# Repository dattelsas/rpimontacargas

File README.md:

# rpimontacargas
Repositorio del Sistemas de Cámaras para Montacargas

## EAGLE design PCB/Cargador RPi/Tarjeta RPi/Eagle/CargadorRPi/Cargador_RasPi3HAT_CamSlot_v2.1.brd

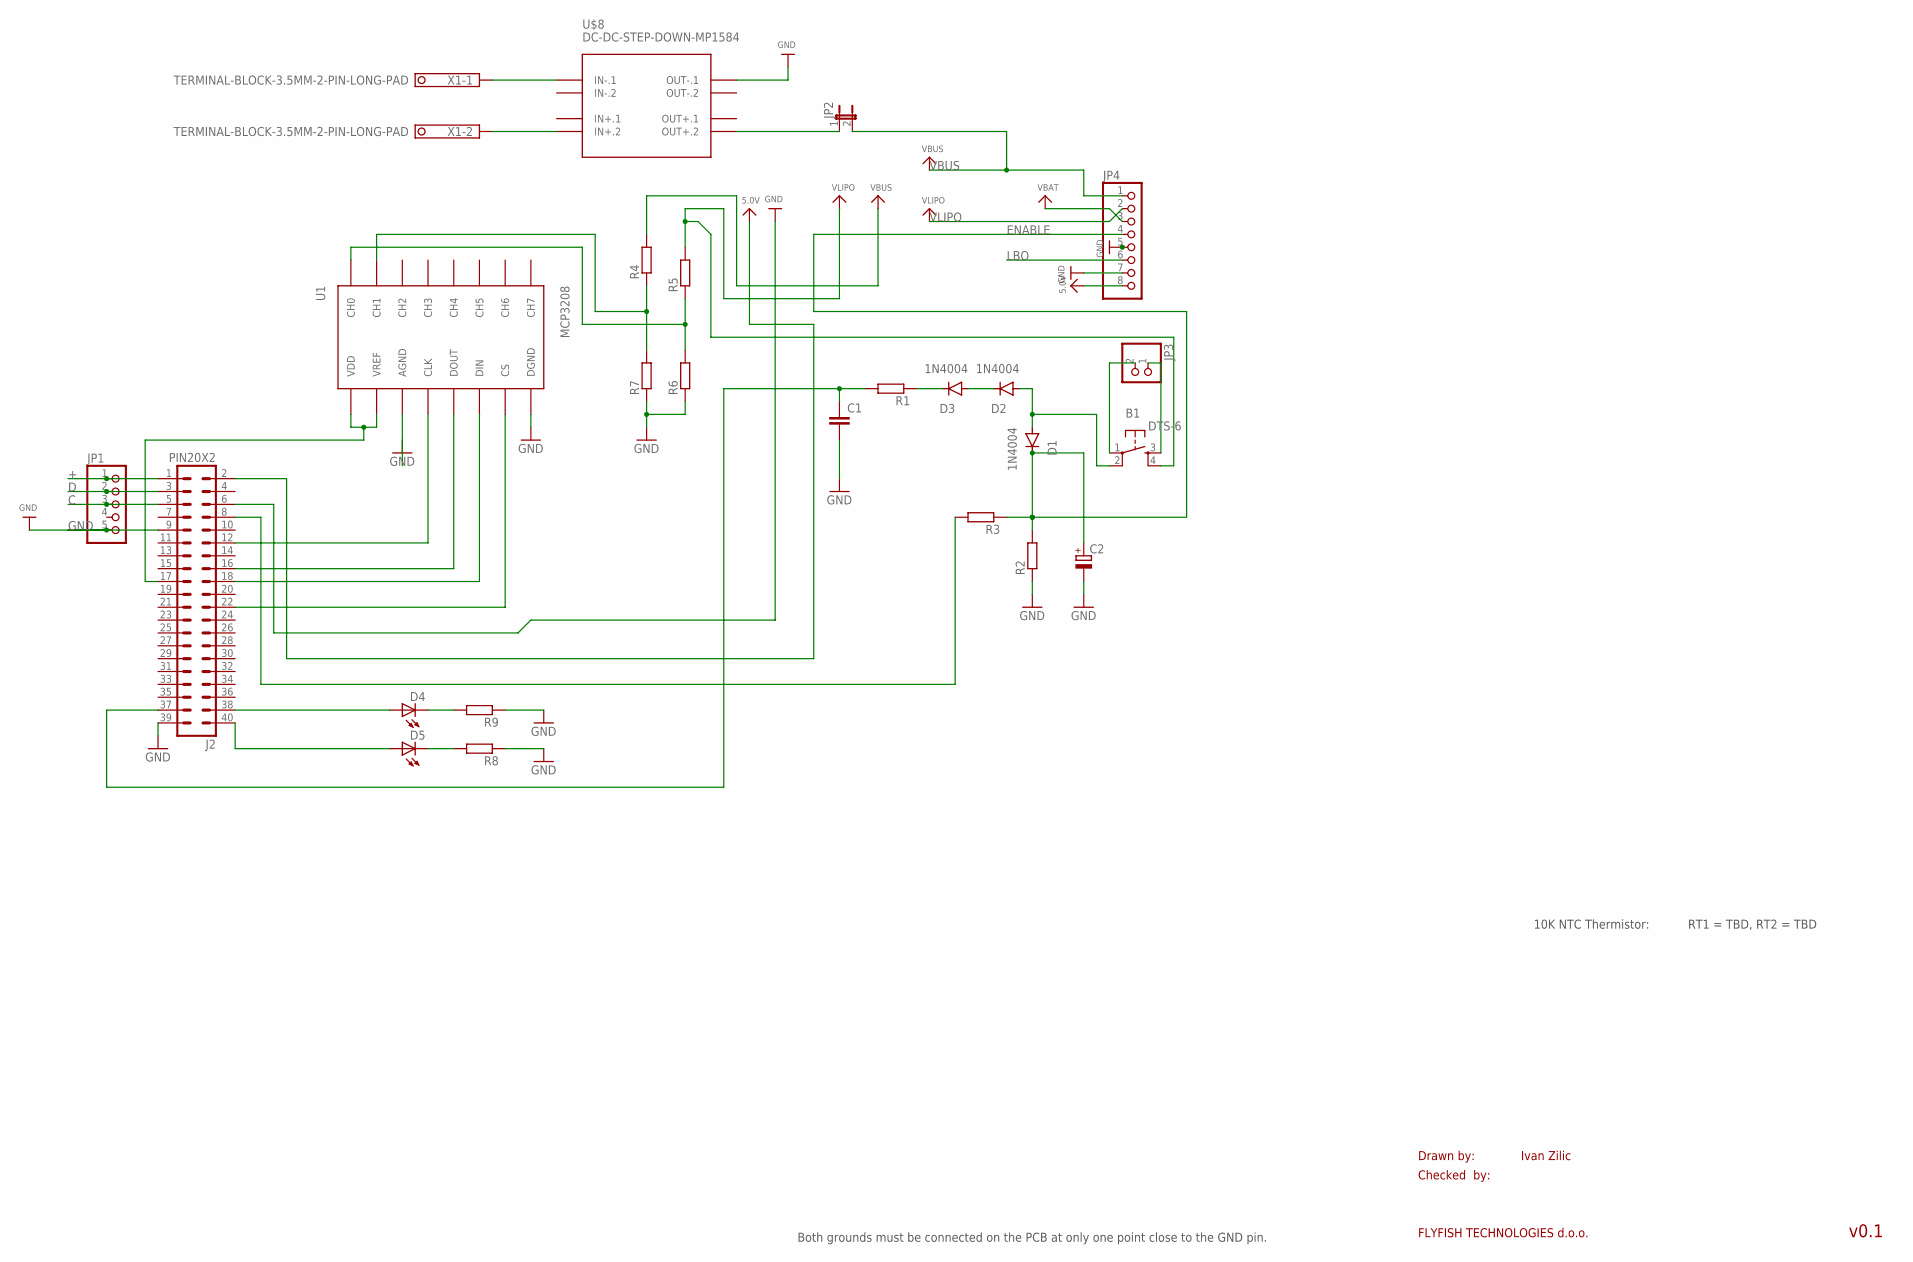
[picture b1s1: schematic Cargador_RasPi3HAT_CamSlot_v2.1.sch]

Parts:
B1: DTS-6
C1: C2.5/2; C2.5-2
C2: CPOL-EUE5-4; E5-4
D1, D2, D3: 1N4004; DO41-10
D4, D5: LED_ELD260; LED_LD260
J2: PIN20X2; PIN_20X2
JP1: PINHD-1X5; 1X05
JP2: JP1E; JP1
JP3: PINHD-1X2; 1X02
JP4: HEADER-1X8; 1X08_OVAL
R1, R2, R3, R4, R5, R6, R7, R8, R9: R-EU_0207/10; 0207/10
U1: MCP3208; DIL16
U$8: DC-DC-STEP-DOWN-MP1584
X1: TERMINAL-BLOCK-3.5MM-2-PIN-LONG-PAD; TERMINAL-BLOCK-2-PIN-3.5MM-LONG-PAD

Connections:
5.0V: J2.2, JP4.8
+: J2.1, JP1.1
C: J2.5, JP1.3
D: J2.3, JP1.2
ENABLE: C2.+, D1.C, JP4.4, R2.2, R3.1
GND: C1.2, C2.-, J2.6, J2.9, J2.39, JP1.5, JP4.5, JP4.7, R2.1, R6.1, R7.1, R8.1, R9.1, U1.AGND, U1.DGND, U$8.OUT-.1
LBO: JP4.6
unnamed: B1.1, JP3.2
unnamed: B1.3, JP3.1
unnamed: D4.K (C), R9.2
unnamed: D5.K (C), R8.2
unnamed: D3.C, R1.1
unnamed: D5.A, J2.40
unnamed: D4.A, J2.38
unnamed: U$8.IN-.1, X1.1
unnamed: U$8.IN+.2, X1.2
unnamed: JP2.1, U$8.OUT+.2
unnamed: J2.17, U1.VDD, U1.VREF
unnamed: R4.1, R7.2, U1.CH1
unnamed: R5.1, R6.2, U1.CH0
unnamed: J2.8, R3.2
unnamed: J2.12, U1.CLK
unnamed: J2.22, U1.CS
unnamed: D2.C, D3.A
unnamed: B1.2, D1.A, D2.A
unnamed: J2.18, U1.DIN
unnamed: J2.16, U1.DOUT
unnamed: C1.1, J2.37, R1.2
VBAT: JP4.3
VBUS: JP2.2, JP4.1, R4.2
VLIPO: B1.4, JP4.2, R5.2

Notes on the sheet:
Drawn by:
Checked by:
FLYFISH TECHNOLOGIES d.o.o.
Ivan Zilic
v0.1
Both grounds must be connected on the PCB at only one point close to the GND pin.
10K NTC Thermistor:
RT1 = TBD, RT2 = TBD

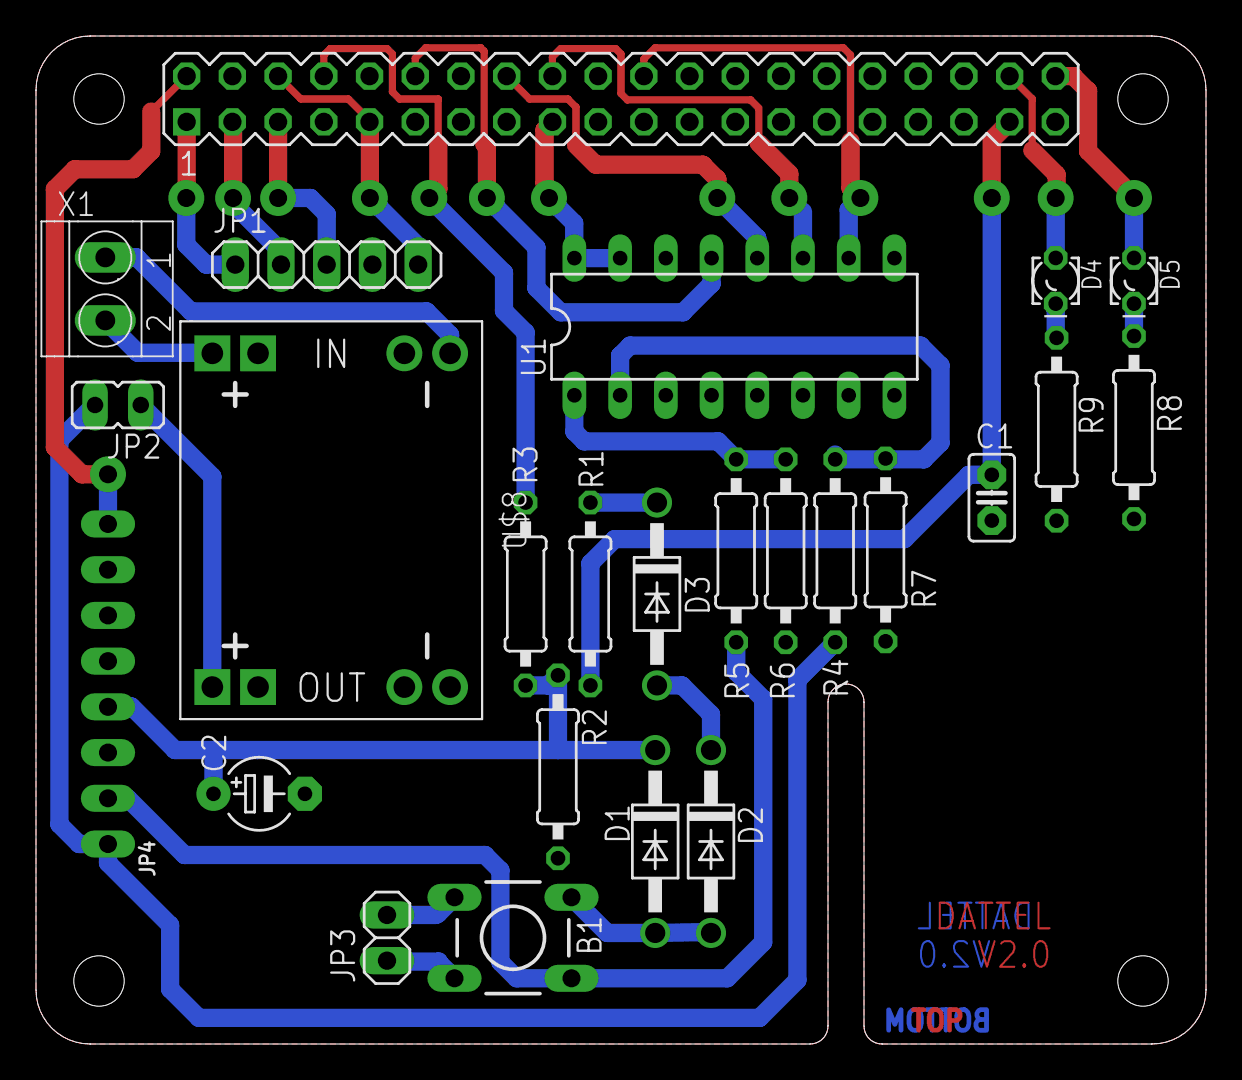
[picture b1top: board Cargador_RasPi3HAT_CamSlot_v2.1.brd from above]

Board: 2 copper layers, 65.0 x 56.0 mm, 25 parts (0 on the bottom side), 29 nets.

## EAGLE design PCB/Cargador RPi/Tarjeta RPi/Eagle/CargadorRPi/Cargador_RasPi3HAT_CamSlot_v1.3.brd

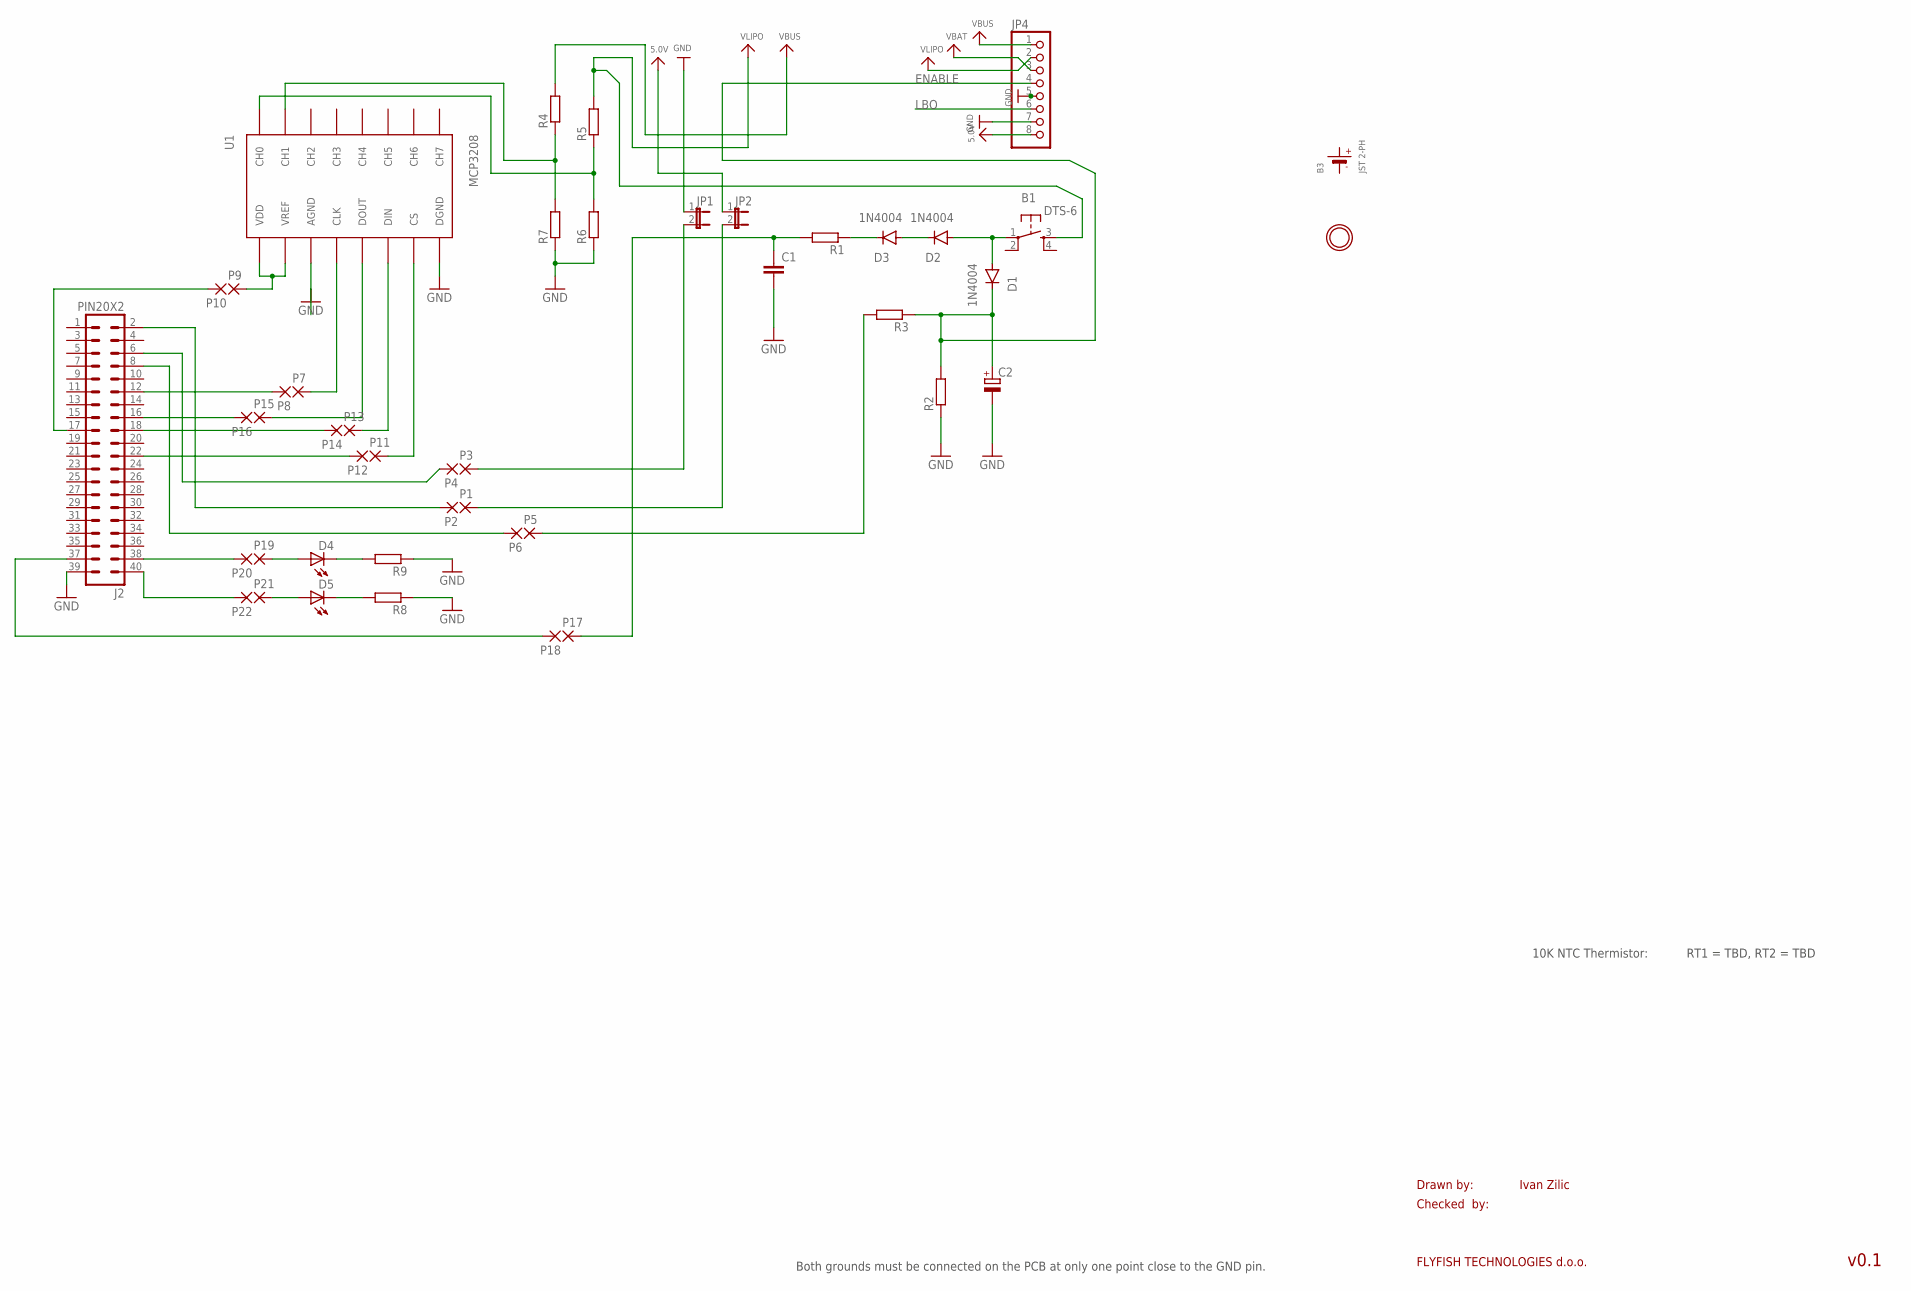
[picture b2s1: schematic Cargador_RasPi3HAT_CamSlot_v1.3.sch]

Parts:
B1: DTS-6
B3: JST 2-PH; JSTPH2
C1: C2.5/2; C2.5-2
C2: CPOL-EUE5-4; E5-4
D1, D2, D3: 1N4004; DO41-10
D4, D5: LED_ELD260; LED_LD260
J2: PIN20X2; PIN_20X2
JP1, JP2: JP1E; JP1
JP4: HEADER-1X8; 1X08_OVAL
P1, P2, P3, P4, P5, P6, P7, P8, P9, P10, P11, P12, P13, P14, P15, P16, P17, P18, P19, P20, P21, P22: 2,15/1,0
R1, R2, R3, R4, R5, R6, R7, R8, R9: R-EU_0207/10; 0207/10
U1: MCP3208; DIL16
U$5: MOUNTINGHOLE2.5; MOUNTINGHOLE_2.5_PLATED

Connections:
5.0V: JP2.1, JP4.8
ENABLE: C2.+, D1.C, JP4.4, R2.2, R3.1
GND: C1.2, C2.-, J2.39, JP1.1, JP4.5, JP4.7, R2.1, R6.1, R7.1, R8.1, R9.1, U1.AGND, U1.DGND
LBO: JP4.6
unnamed: JP1.2, P3.1
unnamed: P5.1, R3.2
unnamed: D4.K (C), R9.2
unnamed: D5.K (C), R8.2
unnamed: D3.C, R1.1
unnamed: J2.40, P22.1
unnamed: J2.38, P20.1
unnamed: P11.1, U1.CS
unnamed: P15.1, U1.DOUT
unnamed: P13.1, U1.DIN
unnamed: P7.1, U1.CLK
unnamed: J2.17, P10.1
unnamed: R4.1, R7.2, U1.CH1
unnamed: R5.1, R6.2, U1.CH0
unnamed: J2.2, P2.1
unnamed: J2.6, P4.1
unnamed: J2.8, P6.1
unnamed: J2.12, P8.1
unnamed: P9.1, U1.VDD, U1.VREF
unnamed: JP2.2, P1.1
unnamed: C1.1, P17.1, R1.2
unnamed: J2.22, P12.1
unnamed: D2.C, D3.A
unnamed: B1.1, D1.A, D2.A
unnamed: J2.18, P14.1
unnamed: J2.16, P16.1
unnamed: J2.37, P18.1
unnamed: D4.A, P19.1
unnamed: D5.A, P21.1
VBAT: JP4.3
VBUS: JP4.1, R4.2
VLIPO: B1.3, JP4.2, R5.2

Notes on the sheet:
Drawn by:
Checked by:
FLYFISH TECHNOLOGIES d.o.o.
Ivan Zilic
v0.1
Both grounds must be connected on the PCB at only one point close to the GND pin.
10K NTC Thermistor:
RT1 = TBD, RT2 = TBD

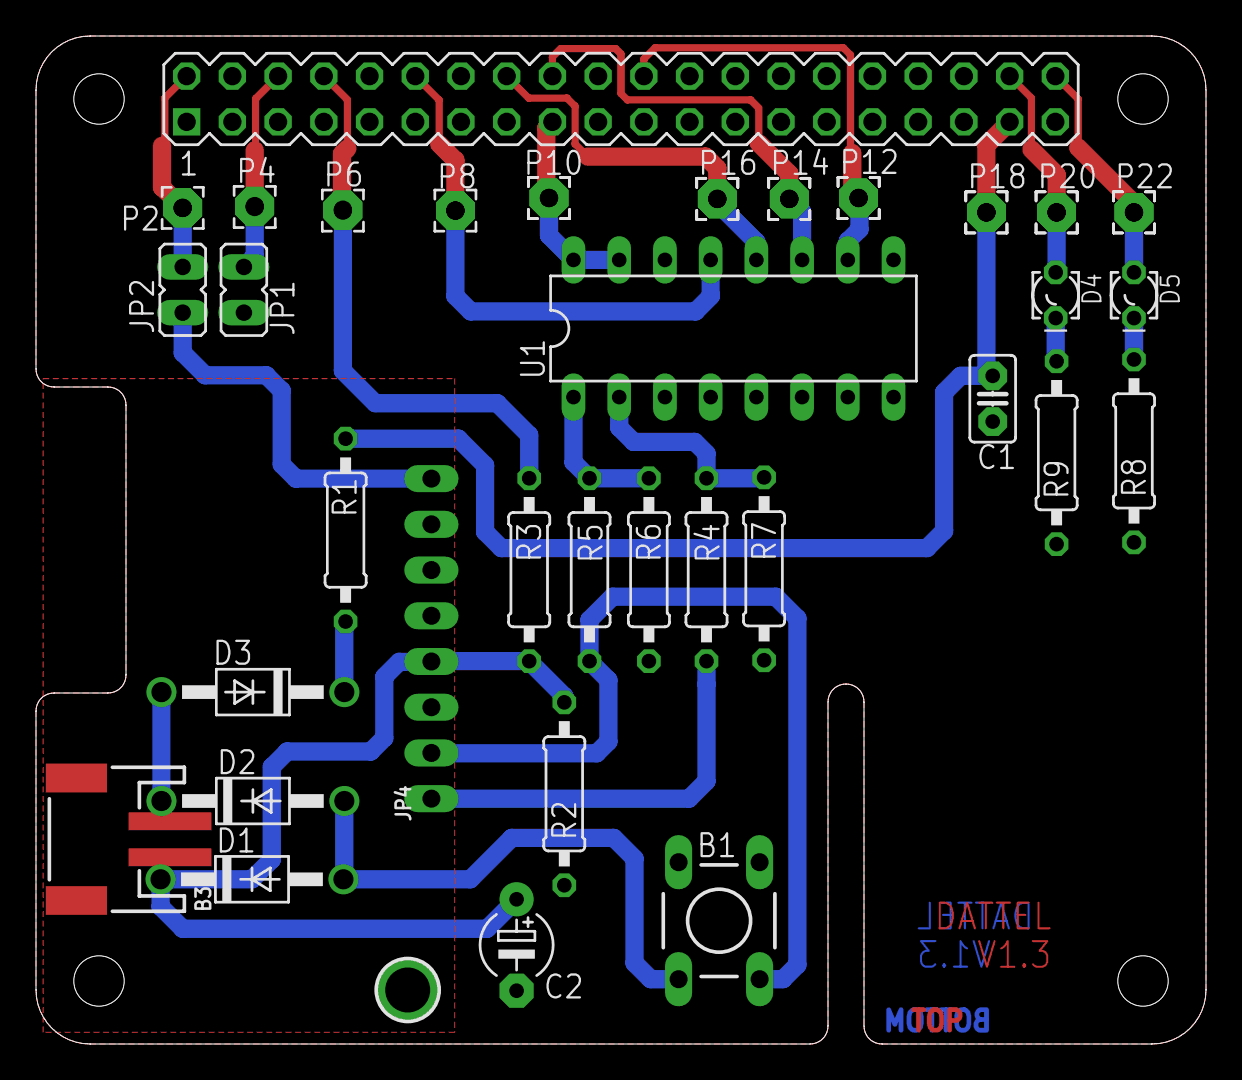
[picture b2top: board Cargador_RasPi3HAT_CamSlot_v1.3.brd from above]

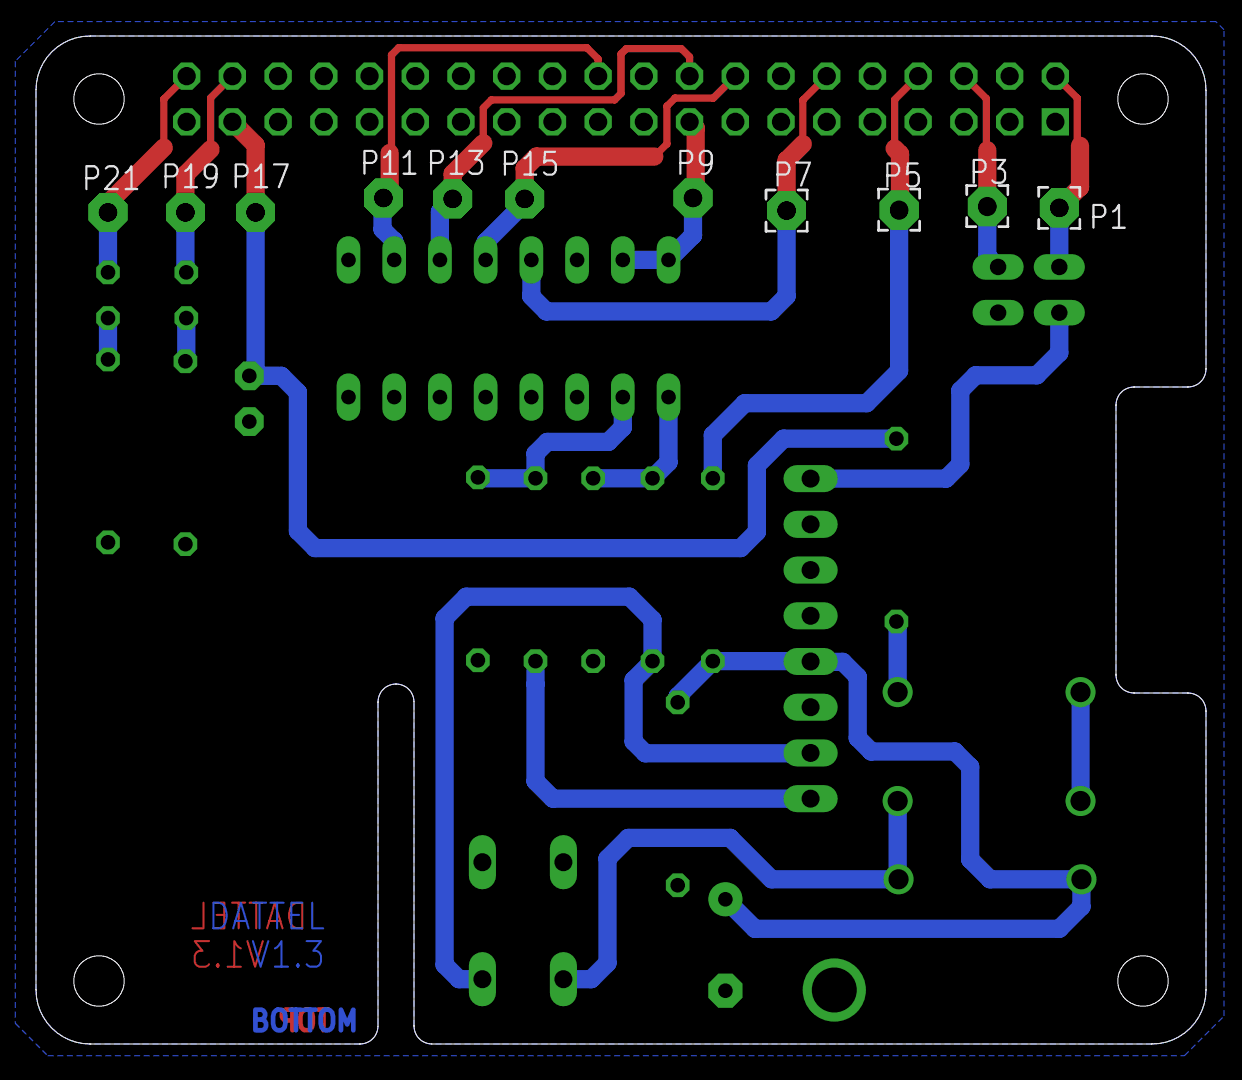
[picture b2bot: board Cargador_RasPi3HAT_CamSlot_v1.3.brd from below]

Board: 2 copper layers, 65.0 x 56.0 mm, 46 parts (4 on the bottom side), 34 nets.

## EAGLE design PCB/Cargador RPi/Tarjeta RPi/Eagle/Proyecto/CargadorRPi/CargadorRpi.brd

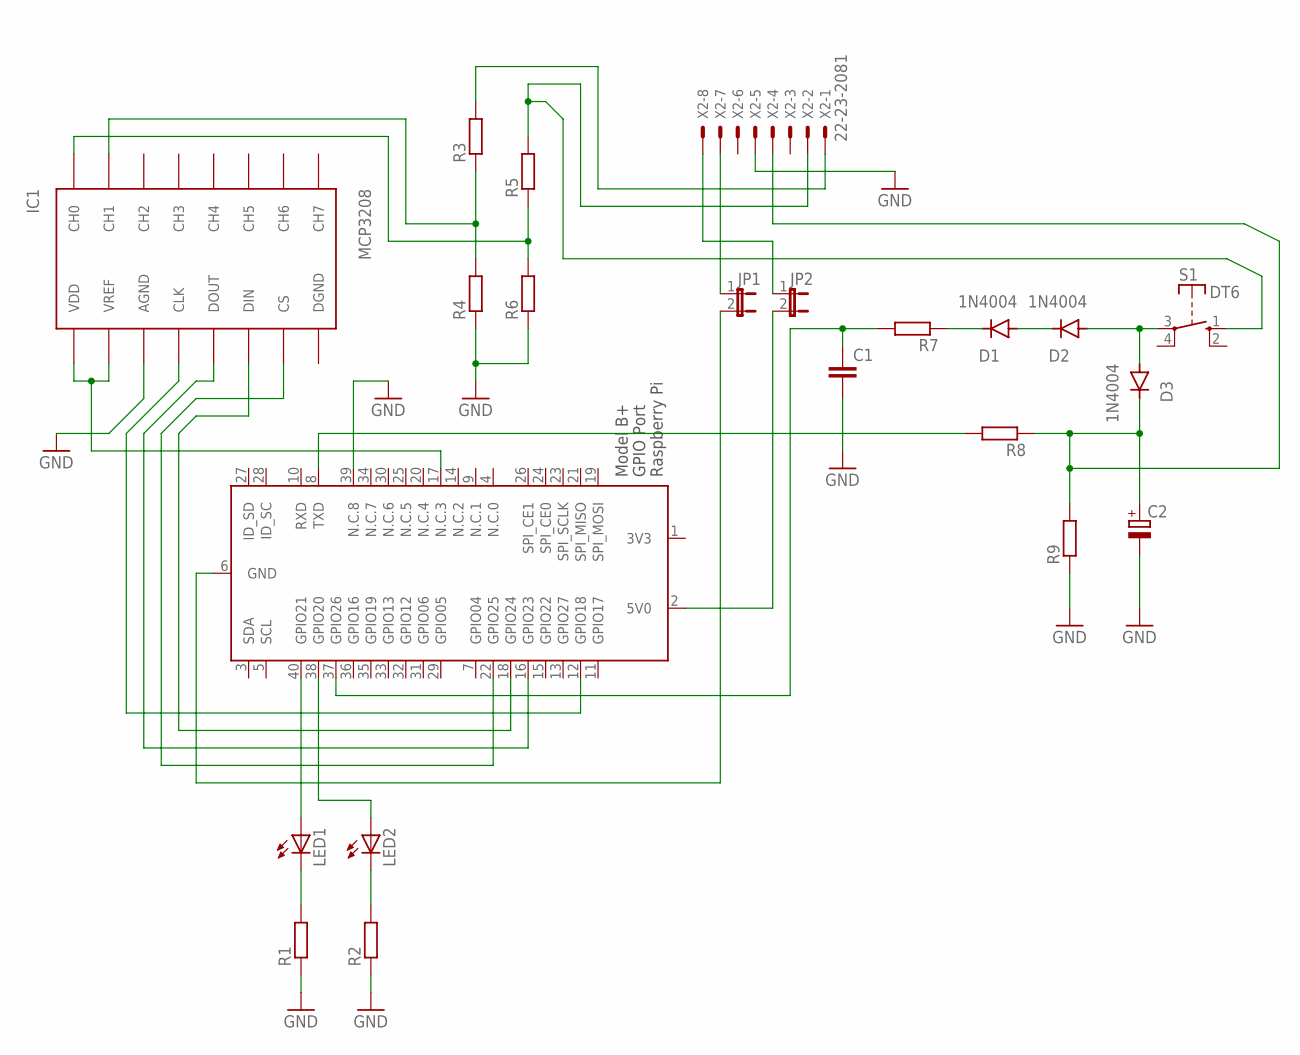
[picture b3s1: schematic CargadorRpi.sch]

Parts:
C1: C2.5/2; C2.5-2
C2: CPOL-EUE5-4; E5-4
D1, D2, D3: 1N4004; DO41-10
IC1: MCP3208; DIL16
JP1, JP2: JP1E; JP1
LED1, LED2: LED_ELD260; LED_LD260
R1, R2, R3, R4, R5, R6, R7, R8, R9: R; R0805
S1: DT6
X1: RASPI_GPIO_B+_PIN
X2: 22-23-2081

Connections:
3V3: X1.1 (3V3)
DGND: IC1.DGND
GND: C1.2, C2.-, IC1.AGND, R1.1, R2.1, R4.1, R6.1, R9.1, X1.39 (N.C.8), X2.5
unnamed: LED1.K (C), R1.2
unnamed: LED2.K (C), R2.2
unnamed: LED1.A, X1.40 (GPIO21)
unnamed: LED2.A, X1.38 (GPIO20)
unnamed: IC1.CS, X1.22 (GPIO25)
unnamed: IC1.DOUT, X1.16 (GPIO23)
unnamed: IC1.DIN, X1.18 (GPIO24)
unnamed: IC1.CLK, X1.12 (GPIO18)
unnamed: IC1.VDD, IC1.VREF, X1.17 (N.C.3)
unnamed: IC1.CH1, R3.1, R4.2
unnamed: IC1.CH0, R5.1, R6.2
unnamed: R3.2, X2.1
unnamed: R5.2, S1.1 (S), X2.2
unnamed: JP1.1, X2.7
unnamed: JP1.2, X1.6 (GND)
unnamed: JP2.1, X2.8
unnamed: JP2.2, X1.2 (5V0)
unnamed: C1.1, R7.2, X1.37 (GPIO26)
unnamed: D1.C, R7.1
unnamed: D1.A, D2.C
unnamed: D2.A, D3.A, S1.3
unnamed: C2.+, D3.C, R8.1, R9.2, X2.4
unnamed: R8.2, X1.8 (TXD)

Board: 2 copper layers, 22 parts (1 on the bottom side), 24 nets, no tracks yet.

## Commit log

2019-01-28 Se agrega archivo .gitignore y se ignora el contenido del directorio Imágenes OS
2019-01-28 Se ignora el contenido del directorio ImgOS
2019-01-28 Se incluyen archivos de diseno del cargador RPi.
2019-01-28 Se actualiza archivo .gitignore
2019-01-28 Diagrama esquemático en Eagle del Cargador RPi.
2019-01-29 Se actualiza el diagrama esquemático del cargador RPi.
2019-01-29 Versión inicial PCB cargador RPi.
2019-01-29 Plantillas PCB HAT
2019-01-29 Se eliminan archivos temporales de proteus
2019-01-29 Se adiciona el archivo explicaci[on scripts oscar paruma
2019-01-30 Se ajusta el diagrama esquemático para utilizar la plantilla RasPi-BplusHAT_CamSlot.sch
2019-01-31 Se borran archivos temporales generados por Eagle.
2019-01-31 Se reemplaza pulsador en el diagrama esquemático.
2019-01-31 Se agrega librería de switches para Eagle.
2019-01-31 Se modifica la PCB aumentando el ancho de los trazos.
2019-01-31 Versión para redistribuir los componentes.
2019-01-31 Se ignoran archivos temporales generados por Eagle y Proteus.
2019-02-02 Ajustes para fabricación de PCB.
2019-02-02 Ajustes teniendo en cuenta la orientación del conector GPIO.
2019-02-02 Se ignora archivo temporal generado por Eagle.
2019-02-07 Se borran versiones no utilizadas y se organiza la estructura de directorios.
2019-02-07 Librería que contiene los holes para los postes del booster.
2019-02-07 Se organiza la estructura de directorios y se genera una nueva versión de la PCB que no requiere through-hole.
2019-02-09 Scripts originales para monitoreo y control del cargador RPi. Ref: https://github.com/craic/pi_power
2019-02-09 Se incluye una validación para mostrar el mensaje y ejecutar shutdown solo después de MAX_COUNTER_LOW_BATTERY voltajes menores al mínimo consecutivos
2019-02-10 Se incluye el archivo la ruta y el nombre del archivo donde se almacenan el valor del voltaje de alimentación de la RPi y su origen (usb o batería) para ser mostrados en la pamtalla del usuario media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
2019-02-10 Se configura el script pi_power_leds.py para que trabaje con leds cátodo común
2019-02-12 Se habilita la opción Shutdown desde la interfaz gráfica para todos los usuarios. El archivo modificado se encuentra en la ruta /usr/local/lib/python2.7/dist-packages/motioneye/templates/main.html
2019-02-14 Ajuste para no duplicar el botón shutdown en la interfaz gráfica cuando se autentica un usuario administrador. El archivo modificado se encuentra en la ruta /usr/local/lib/python2.7/dist-packages/mot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
2019-02-14 Ajuste para que la acción asociada al botón shutdown en la interfaz gráfica la pueda ejecutar un usuario no administrador. El archivo modificado se encuentra en la ruta /usr/local/lib/python2.7/dist-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
2019-02-14 Archivo de configuración de motioneye.
2019-02-15 Librería con modelos de tarjeta HAT adicionales
2019-02-15 Se elimina el sript base para lograr la visualización del nivel de batería desde la pantalla de MotionEye
2019-02-15 Librería que contiene el modelo completo de la RPi
2019-02-15 Librería con el modelo del conector micro USB
2019-02-15 Script que permite visualizar en pantalla el voltaje con el que opera el circuito cargador de la RPi. Lee la información del archivo que genera el script pi_power.py
2019-02-15 Modelos para imprimir en 3D de una caja para RPi
2019-02-15 Se incluye las instrucciones y fuentes de consulta para realizar el apagado del WiFi y Bluetooth propios de la RPi (OnBoard)
2019-02-15 Se incluyen al PCB "vias" para reemplazar la necesidad de Through-Hole para acceder a los pines del puerto GPIO de la RPi
2019-02-15 Versión 2.0: Incluye el conector micro USB para poder alimentar la tarjeta con un Power Bank e incluye el reloj de tiempo real. Contiene "vias" como reemplazo del through-hole para el puerto GPIO de 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
2019-02-15 Se mejoran algunas pistas del PCB
2019-02-16 Se ajustan los "via" que reemplazan el through-hole para que tengan una superficie en cobre para la soldadura
2019-02-16 Archivo para la toma de datos de tiempos de descarga de las baterías LiPo. Datos disponibles 9, 10 y 15 de febrero de 2019.
2019-05-02 Ajuste en la ubicación del booster
2019-05-02 Ajuste en la ubicación del puerto micro USB
2019-05-02 Creación de la fuente para RPi que inlcuye un conversor DC-DC o buck
2019-05-02 Creación de la PCB para el extensor USB para conexión de la Antena WiFi externa
2019-05-02 Librerías reubicadas en la carpeta general de Eagle

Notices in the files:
parts and their libraries:
microbuilder: This work is placed in the public domain, and may be freely used for commercial and non-commercial work with the following conditions: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
diy-modules: Released under the Creative Commons Attribution 4.0 International License: http://creativecommons.org/licenses/by/4.0
